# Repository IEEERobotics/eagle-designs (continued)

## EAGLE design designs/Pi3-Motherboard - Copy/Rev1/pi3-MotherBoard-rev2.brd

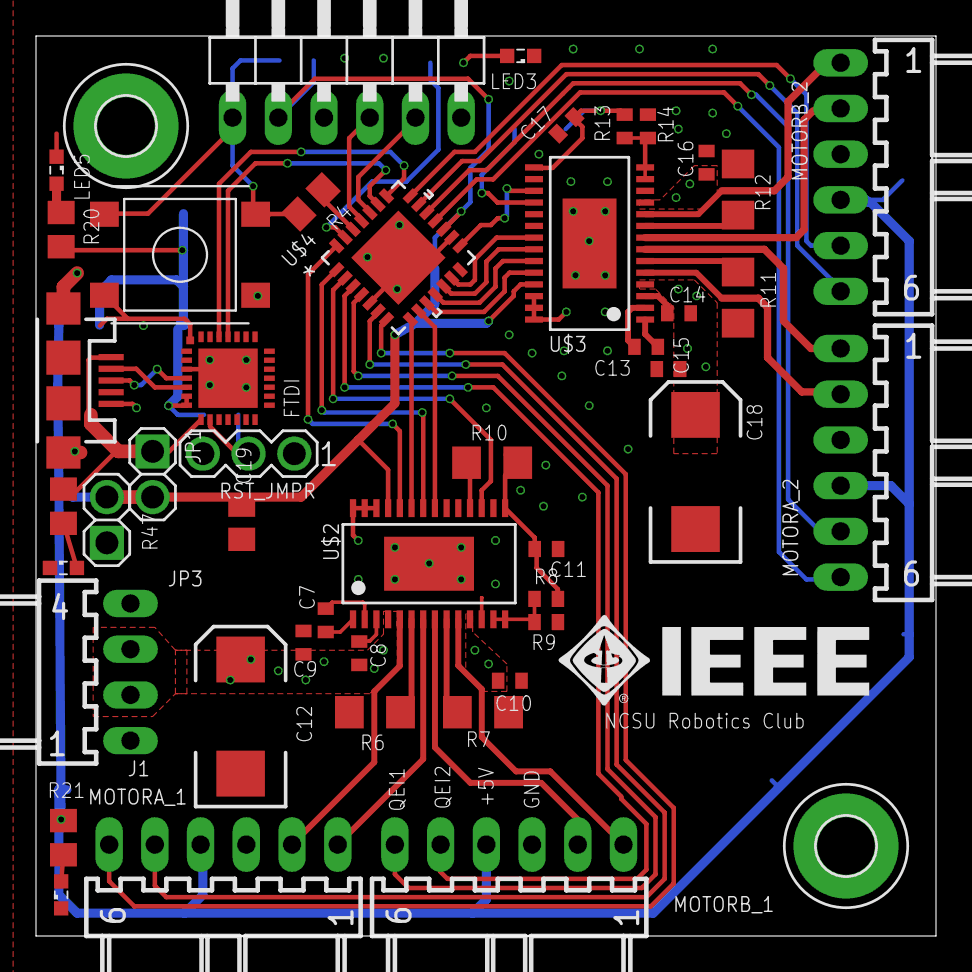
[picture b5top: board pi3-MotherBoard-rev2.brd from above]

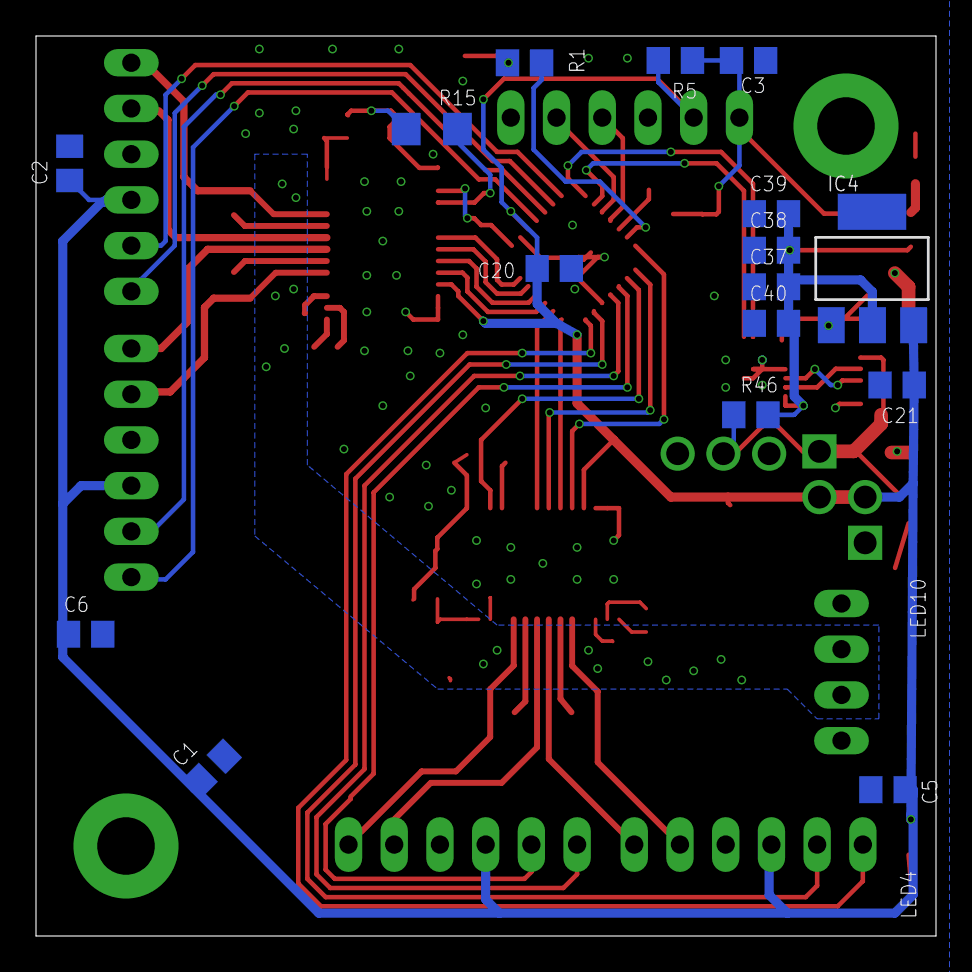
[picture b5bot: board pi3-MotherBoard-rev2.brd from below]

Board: 2 copper layers, 50.0 x 50.0 mm, 64 parts (16 on the bottom side), 61 nets.

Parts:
BT_USB_MICROB1: USB-MICROB
C1, C2, C3, C5, C6, C19, C20, C38, C39: 0.1uF; C0805
C7, C9, C10, C11, C13, C15, C16, C17: 0.1uF; C0402
C8, C14: 0.47uF; C0402
C12, C18: 100uF; EIA7343
C21: 4.7 uF; C0805
C37: 1uF; C0805
C40: 4.7uF; C0805
FTDI: CP2102; MLP28
H1, H3: MOUNT-PAD-ROUND3.2; 3,2-PAD
IC4: REG1117; SOT223
J1: 22-05-7048-04; 7395-04
JP1, JP3: 1X02
JP11: 1X06/90
LED3, LED4, LED5, LED10: SML0603
MOTORA_1, MOTORA_2: 22-05-7068-06; 7395-06
MOTORB_1, MOTORB_2: 22-05-7068-06; 7395-06
R1, R5, R20, R21: 10K; R0805
R4: 100; R0805
R6, R7, R11, R12: 0.1; R1206
R8, R13: 10k; R0402
R9, R14: 15k; R0402
R10, R15: 10K; R1206
R46: 1k; R0805
R47: 500; R0805
RST_JMPR: MA03-1
TOUCH_RESET: RESET; MC32882_FINAL
U$1: LOGO; IEEE-LOGO
U$2, U$3: DRV8881PPWPR; TSSOP-28
U$4: PIC16F72-I/ML; QFN65P600X600X100-28N

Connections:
+3V3: C37.2, C38.2, C39.2, C40.2, FTDI.6, FTDI.7, IC4.2, R20.2, R46.2
+5V: C1.1, C2.1, C5.1, C6.1, C19.1, C20.1, C21.1, IC4.3, JP1.2, JP3.2, JP11.2, MOTORA_1.4, MOTORA_2.4, MOTORB_1.4, MOTORB_2.4, R5.2, R21.2, U$2.25, U$3.25, U$4.17
+7V: C8.2, C9.1, C10.1, C12.A, C14.2, C15.1, C16.1, C18.A, J1.2, J1.3, U$2.4, U$2.11, U$3.4, U$3.11
AEN_1: U$2.23, U$4.8
AEN_2: U$3.23, U$4.11
APH_1: U$2.24, U$4.28
APH_2: U$3.24, U$4.10
BEN_1: U$2.21, U$4.9
BEN_2: U$3.21, U$4.13
BPH_1: U$2.22, U$4.1
BPH_2: U$3.22, U$4.12
BT_D+: BT_USB_MICROB1.D+, FTDI.4
BT_D-: BT_USB_MICROB1.D-, FTDI.5
GND: BT_USB_MICROB1.GND, BT_USB_MICROB1.MT1, BT_USB_MICROB1.MT2, C1.2, C2.2, C3.2, C5.2, C6.2, C9.2, C10.2, C11.2, C12.C, C15.2, C16.2, C17.2, C18.C, C19.2, C20.2, C21.2, C37.1, C38.1, C39.1, C40.1, FTDI.3, FTDI.EXP, FTDI.M, H1.B3,2, H3.B3,2, IC4.1, J1.1, J1.4, JP3.1, JP11.3, LED3.C, LED4.C, LED5.C, LED10.C, MOTORA_1.3, MOTORA_2.3, MOTORB_1.3, MOTORB_2.3, R6.2, R7.2, R9.2, R11.2, R12.2, R14.2, RST_JMPR.3, TOUCH_RESET.P$1, TOUCH_RESET.P$4, U$2.12, U$2.26, U$2.27, U$2.28, U$2.EXP, U$3.12, U$3.26, U$3.27, U$3.28, U$3.EXP, U$4.5, U$4.16, U$4.29
ICDCLK: JP11.5, U$4.24
ICDDAT: JP11.4, U$4.25
MCLR: C3.1, JP11.1, R4.2, R5.1, TOUCH_RESET.P$2, TOUCH_RESET.P$3
MCLR`: R4.1, U$4.26
MOTOR1A_1: MOTORA_1.2, U$2.5
MOTOR1A_2: MOTORA_1.1, U$2.7
MOTOR1B_1: MOTORB_1.2, U$2.8
MOTOR1B_2: MOTORB_1.1, U$2.10
MOTOR2A_1: MOTORA_2.2, U$3.5
MOTOR2A_2: MOTORA_2.1, U$3.7
MOTOR2B_1: MOTORB_2.2, U$3.8
MOTOR2B_2: MOTORB_2.1, U$3.10
unnamed: LED3.A, R1.1
unnamed: R7.1, U$2.9
unnamed: LED5.A, R20.1
unnamed: LED4.A, R21.1
unnamed: FTDI.9, R46.1, RST_JMPR.2
unnamed: LED10.A, R47.1
unnamed: R6.1, U$2.6
unnamed: C7.2, U$2.2
unnamed: C7.1, U$2.1
unnamed: C8.1, U$2.3
unnamed: R8.2, R9.1, U$2.13, U$2.14
unnamed: R12.1, U$3.9
unnamed: R11.1, U$3.6
unnamed: C13.2, U$3.2
unnamed: C13.1, U$3.1
unnamed: C14.1, U$3.3
unnamed: R13.2, R14.1, U$3.13, U$3.14
NFAULT_1: R10.1, U$2.18
NFAULT_2: R15.1, U$3.18
NSLEEP_1: U$2.17, U$4.2
NSLEEP_2: U$3.17, U$4.15
QEIA1_1: MOTORA_1.5, U$4.6
QEIA1_2: MOTORA_1.6, U$4.7
QEIA2_1: MOTORA_2.5, U$4.19
QEIA2_2: MOTORA_2.6, U$4.18
QEIB1_1: MOTORB_1.5, U$4.3
QEIB1_2: MOTORB_1.6, U$4.4
QEIB2_1: MOTORB_2.5, U$4.21
QEIB2_2: MOTORB_2.6, U$4.20
RX: FTDI.26, U$4.22
STATUS1: R1.2, U$4.27
TX: FTDI.25, U$4.23
V3P3_1: C11.1, R8.1, R10.2, U$2.15
V3P3_2: C17.1, R13.1, R15.2, U$3.15
VBUS: BT_USB_MICROB1.VBUS, FTDI.8, JP1.1, R47.2
